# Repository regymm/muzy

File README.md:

# MUZY

AMD/Xilinx ZYNQ 7010/7020 SoC as generic FPGA development board, no DDR -- cheaper than your Artix 7! 

## MUZY-2

[BGA on 2-layers? It's possible and verified!](muzy2.md)

## MUZY-4

[Now on sale!]()

**Hardware**

- Zynq 7020 (xc7z020-clg400-1)

- RP2040-based JTAG blaster, with DirtyJTAG / XVC Pico firmware, working with OpenFPGALoader and Vivado

- Dual SD Card PS + PL

- Dual Video Out HDMI + VGA 

- Dual USB Host

- Dual PMOD

- 2 switches, 2 buttons, 4 LEDs

- 256 Mb (32 MB) SDRAM

Should be perfect for SoC development & work as a handhold FPGA computer! 

Open-source [Zynq](https://github.com/regymm/GenZ)/[FPGA](https://github.com/OpenXC7) toolchains recommended! 

**JTAG**

There're 3 ways to program the FPGA by JTAG: 

1. Use the standard 2x5 pin header with an external Xilinx dongle.
2. Use the on-board pluggable RP2040 module and [the dirtyJtag firwmare](https://github.com/regymm/pico-dirtyJtag), `./pico_fw/dirtyJtag.uf2`. This supports `openFPGALoader -c dirtyJtag bitstream.bit` style direct programming. Simultaneous UART access also available, usually `/dev/ttyACM0`. Vivado access (and thus ILA) not supported by this firmware. 
3. Use the on-board pluggable RP2040 module and [the xvcPico firmware](https://github.com/regymm/xvc-pico), `./pico_fw/xvcPico.uf2`. Then, launch the daemon in xvcPico (`xvcd-pico`) and 127.0.0.1:2542 for XVC access in Vivado. openFPGALoader can still be used with `openFPGALoader -c xvc-client  --ip 127.1 --port 2542 bitstrea.bit`. Simultaneous UART access also available, usually `/dev/ttyACM0`. 

- For RP Pico firmware update, press the BOOT button down while connecting the USB-C cable, a USB-like device will show up on PC for firmware uploading. 

**Software**

Tested: [Zynq PS No-DDR SD Boot](https://github.com/regymm/GenZ/tree/master/examples/6-noddr-sdboot), [RISC-V SoC Linux booting from SD Card](https://github.com/regymm/quasiSoC/tree/master/rtl/hart_transplant/openla500), Dual video output

**Gallery**

Video: [Linux UART with dual graphics test output](https://www.youtube.com/shorts/H9cZ7YbqNOI)

Pictures:

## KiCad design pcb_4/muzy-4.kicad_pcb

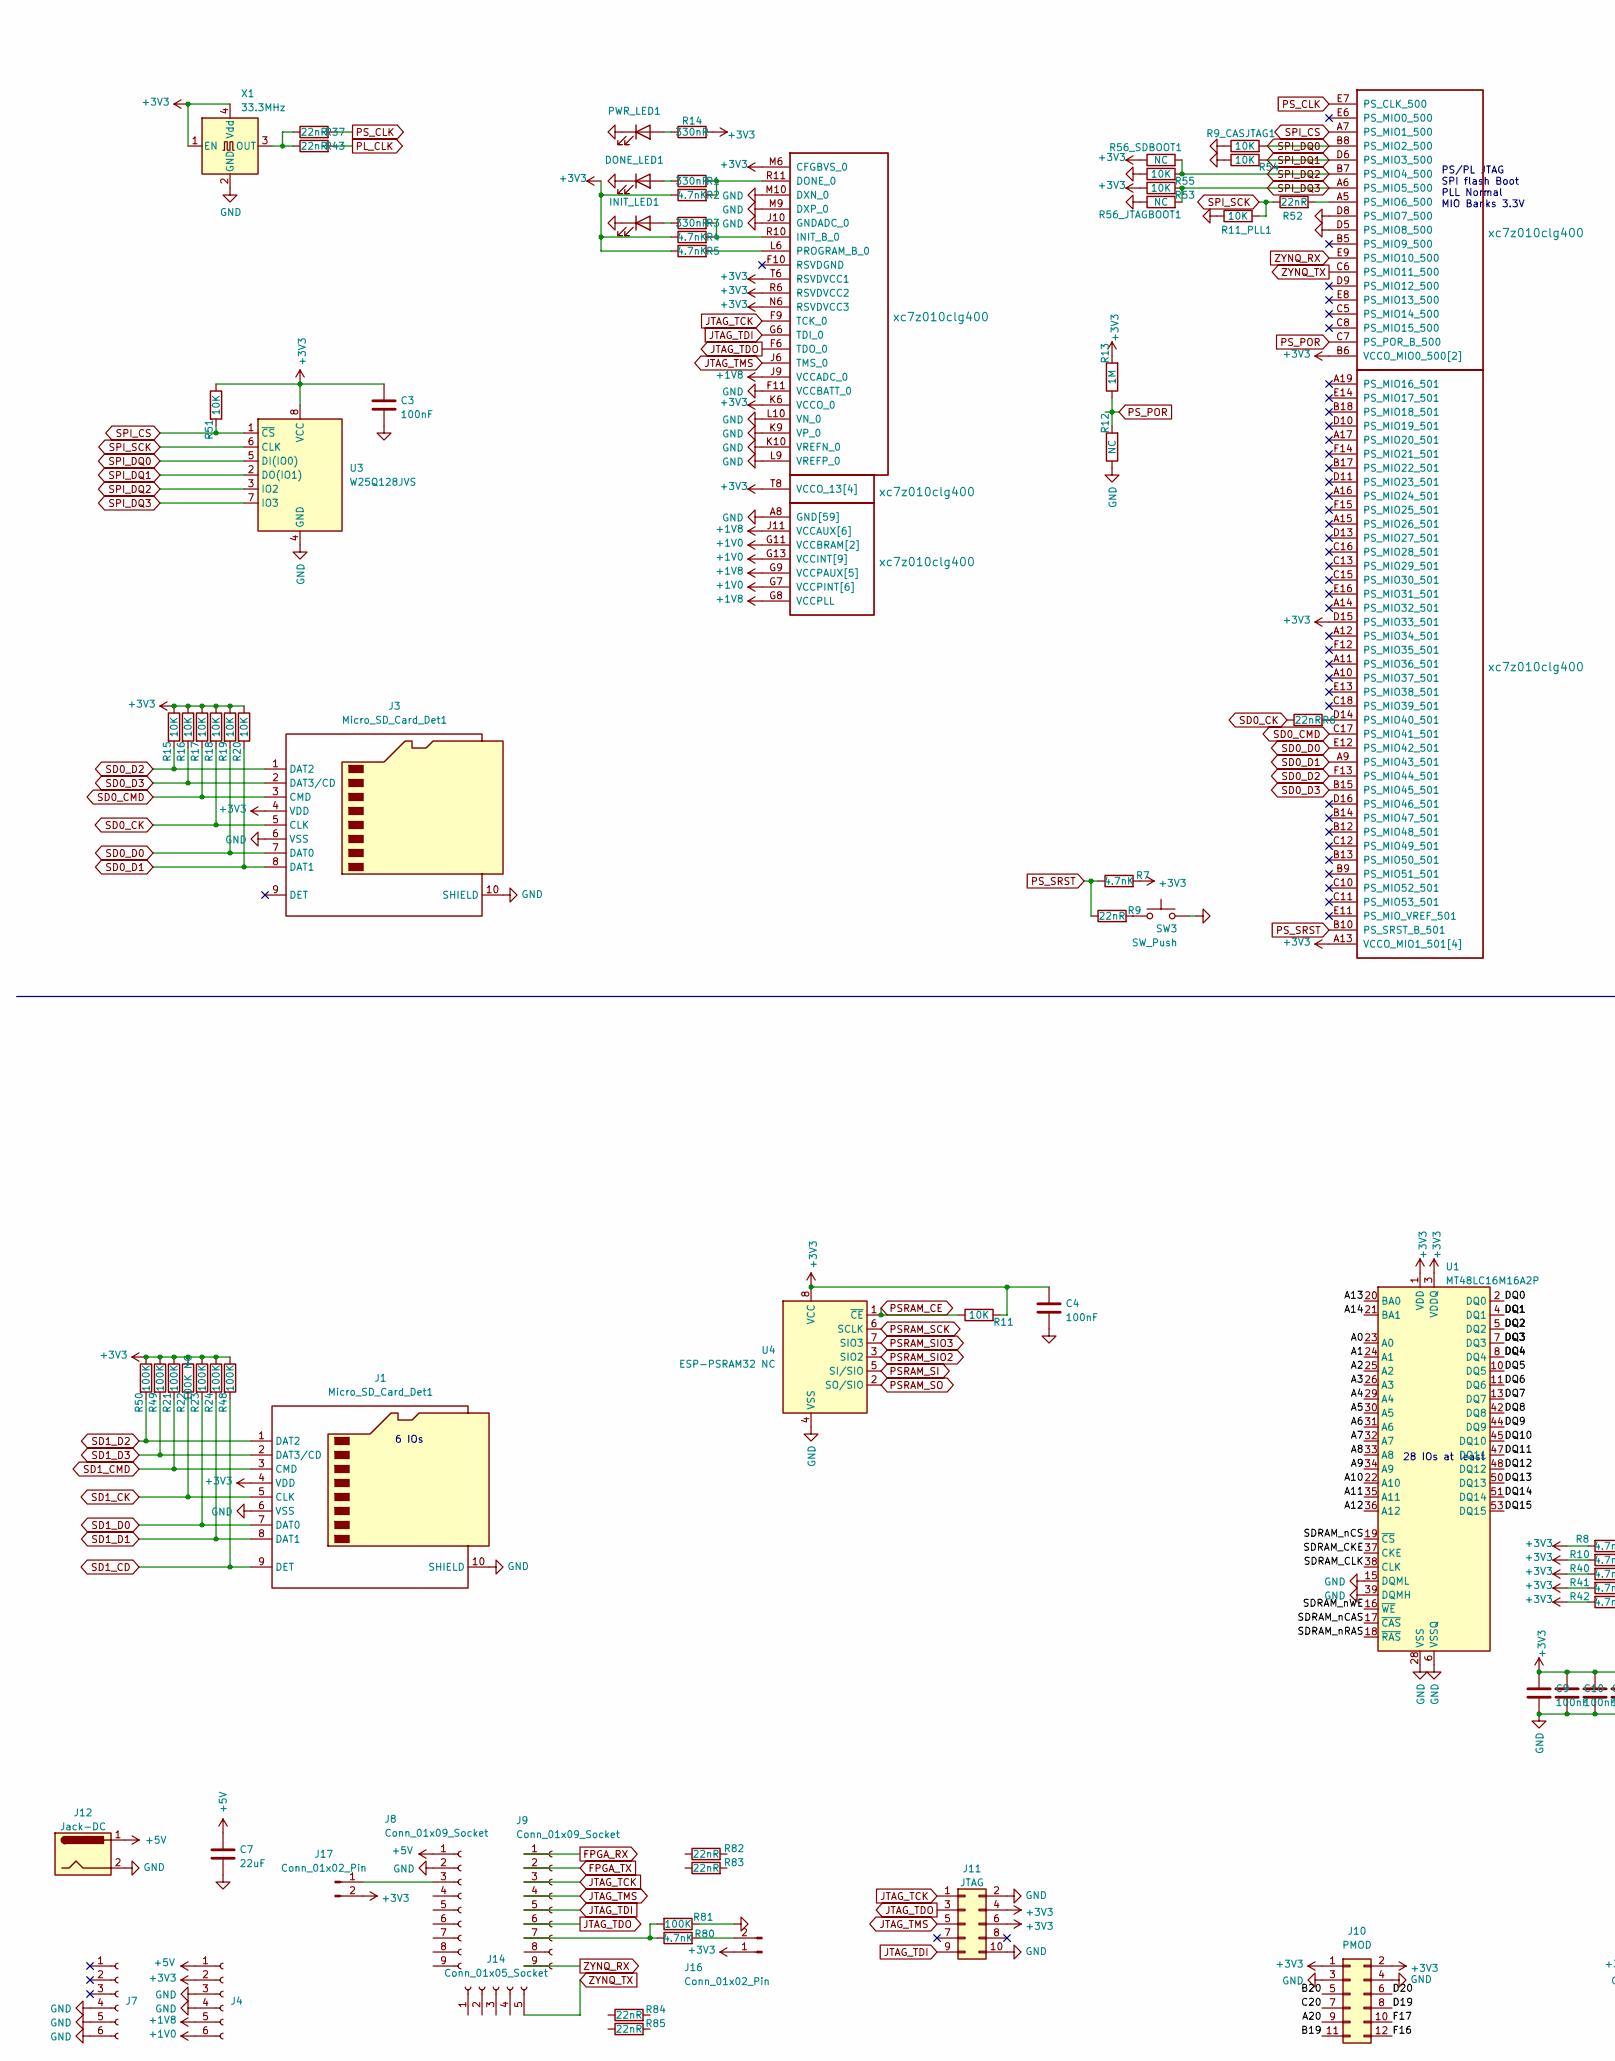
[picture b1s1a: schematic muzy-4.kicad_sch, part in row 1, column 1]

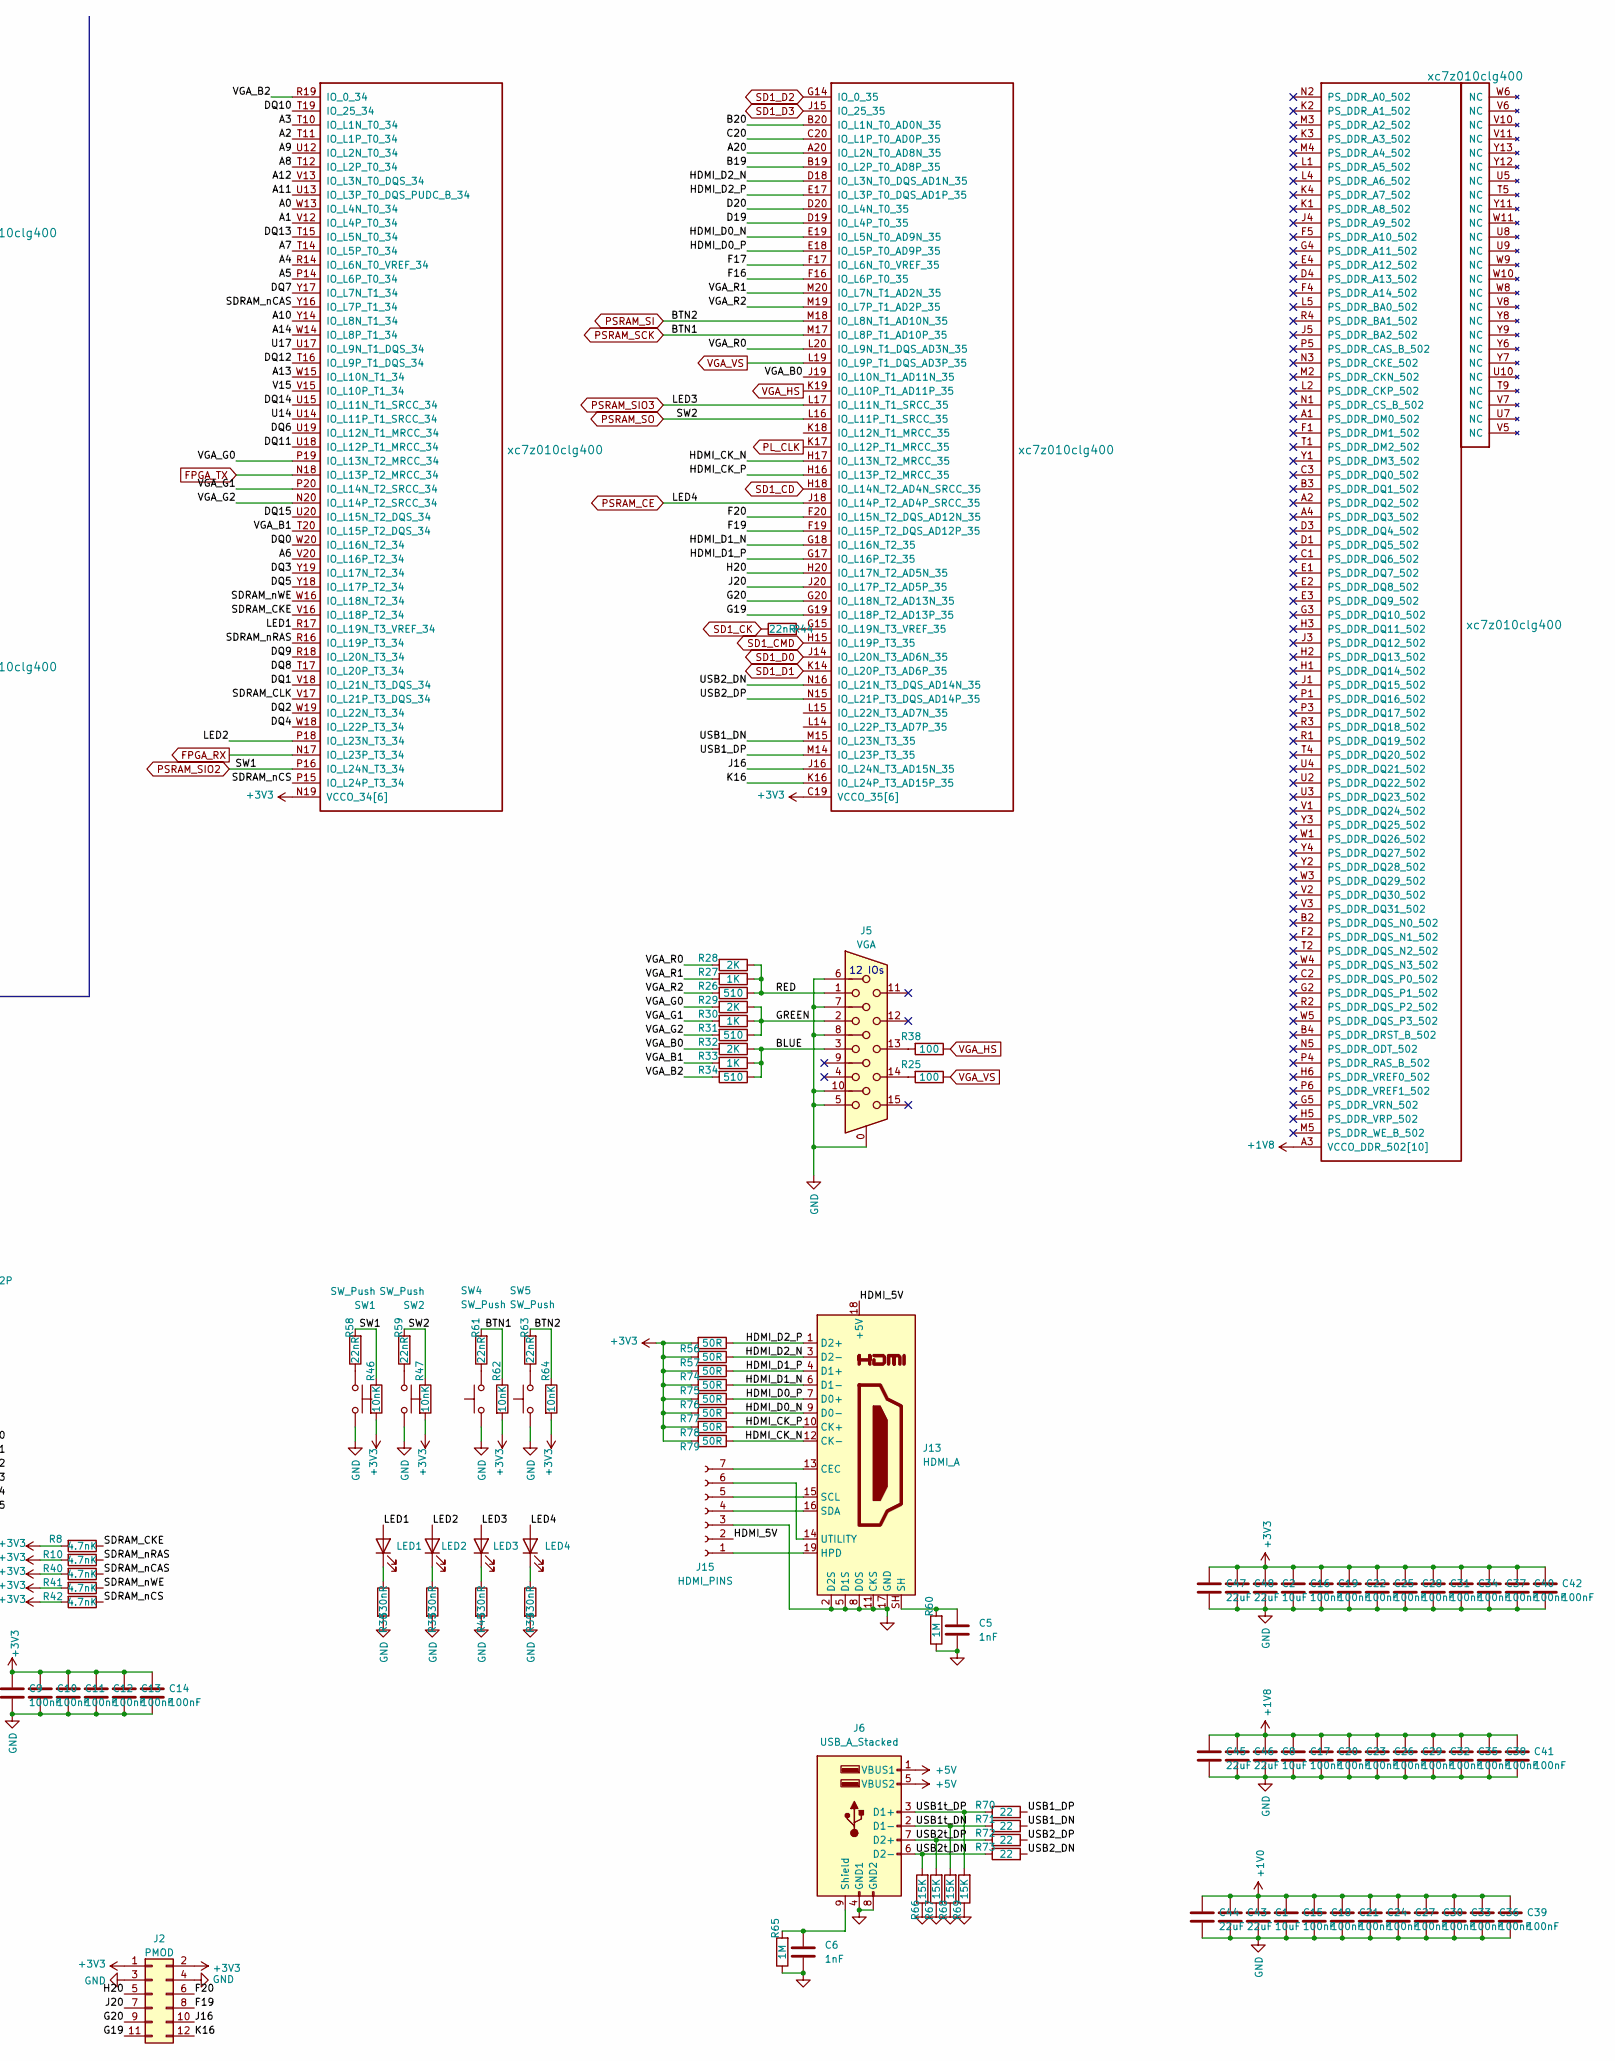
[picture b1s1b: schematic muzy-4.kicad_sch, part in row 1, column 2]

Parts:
C1, C2, C8: 10uF; C_0402_1005Metric
C3, C4, C9, C10, C11, C12, C13, C14, C15, C16, C17, C18, C19, C20, C21, C22, C23, C24, C25, C26, C27, C28, C29, C30, C31, C32, C33, C34, C35, C36, C37, C38, C39, C40, C41, C42: 100nF; C_0402_1005Metric
C5, C6: 1nF; C_0402_1005Metric
C7, C43, C44, C45, C46, C47, C48: 22uF; C_0603_1608Metric
DONE_LED1: LED; LED_0603_1608Metric_Pad1.05x0.95mm_HandSolder
INIT_LED1: LED; LED_0603_1608Metric_Pad1.05x0.95mm_HandSolder
J1, J3: Micro_SD_Card_Det1; SDMICRO_AT
J2, J10: PMOD; PinSocket_2x06_P2.54mm_Horizontal
J4, J7: Conn_01x06_Socket; PinSocket_1x06_P2.54mm_Vertical
J5: VGA; DSUB-15-HD_Female_Horizontal_P2.29x1.98mm_EdgePinOffset3.03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
J6: USB_A_Stacked; USB_A_CUI_UJ2-ADH-TH_Horizontal_Stacked
J8, J9: Conn_01x09_Socket; PinSocket_1x09_P2.54mm_Vertical
J11: JTAG; PinHeader_2x05_P2.54mm_Vertical
J12: Jack-DC; BarrelJack_Wuerth_6941xx301002
J13: HDMI_A; HDMI_A_Molex_208658-1001_Horizontal
J14: Conn_01x05_Socket; PinSocket_1x05_P2.54mm_Vertical
J15: HDMI_PINS; PinSocket_1x07_P1.00mm_Vertical
J16, J17: Conn_01x02_Pin; PinHeader_1x02_P2.54mm_Vertical
LED1, LED2, LED3, LED4: LED; LED_0603_1608Metric_Pad1.05x0.95mm_HandSolder
PWR_LED1: LED; LED_0603_1608Metric_Pad1.05x0.95mm_HandSolder
R1, R3, R14, R35, R36, R39, R45: 330nR; R_0402_1005Metric
R2, R4, R5, R7, R8, R10, R40, R41, R42, R80: 4.7nK; R_0402_1005Metric
R6, R9, R37, R43, R44, R52, R58, R59, R61, R63, R82, R83, R84, R85: 22nR; R_0402_1005Metric
R9_CASJTAG1, R11, R11_PLL1, R15, R16, R17, R18, R19, R20, R51, R53, R54, R55: 10K; R_0402_1005Metric
R12: NC; R_0402_1005Metric_Pad0.72x0.64mm_HandSolder
R13, R65: 1M; R_0402_1005Metric
R21, R23, R24, R48, R49, R50, R81: 100K; R_0402_1005Metric
R22: 100K NC; R_0402_1005Metric
R25, R38: 100; R_0402_1005Metric
R26, R31, R34: 510; R_0402_1005Metric
R27, R30, R33: 1K; R_0402_1005Metric
R28, R29, R32: 2K; R_0402_1005Metric
R46, R47, R62, R64: 10nK; R_0402_1005Metric
R56, R57, R74, R75, R76, R77, R78, R79: 50R; R_0402_1005Metric
R56_JTAGBOOT1, R56_SDBOOT1: NC; R_0402_1005Metric
R60: 1M; R_0402_1005Metric_Pad0.72x0.64mm_HandSolder
R66, R67, R68, R69: 15K; R_0402_1005Metric
R70, R71, R72, R73: 22; R_0402_1005Metric
SW1, SW2: SW_Push; SW_Slide-03_Wuerth-WS-SLTV_10x2.5x6.4_P2.54mm
SW3, SW4, SW5: SW_Push; SW_Push_SPST_NO_Alps_SKRK
U1: MT48LC16M16A2P; TSOP-II-54_22.2x10.16mm_P0.8mm
U2: xc7z010clg400; Xilinx_CLG400_NoPaste_JLC_Package_Delay
U3: W25Q128JVS; SOIC-8_5.23x5.23mm_P1.27mm
U4: ESP-PSRAM32 NC; SOIC-8_3.9x4.9mm_P1.27mm
X1: 33.3MHz; Crystal_SMD_3225-4Pin_3.2x2.5mm

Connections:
+1V0: C1.1, C15.1, C18.1, C21.1, C24.1, C27.1, C30.1, C33.1, C36.1, C39.1, C43.1, C44.1, J4.6, U2.G7 (VCCPINT[6]), U2.G11 (VCCBRAM[2]), U2.G13 (VCCINT[9]), U2.H10 (VCCBRAM[2]), U2.H12 (VCCINT[9]), U2.J7 (VCCPINT[6]), U2.J13 (VCCINT[9]), U2.K12 (VCCINT[9]), U2.L7 (VCCPINT[6]), U2.L13 (VCCINT[9]), U2.M12 (VCCINT[9]), U2.N7 (VCCPINT[6]), U2.N13 (VCCINT[9]), U2.P8 (VCCPINT[6]), U2.P12 (VCCINT[9]), U2.R7 (VCCPINT[6]), U2.R13 (VCCINT[9])
+1V8: C8.1, C17.1, C20.1, C23.1, C26.1, C29.1, C32.1, C35.1, C38.1, C41.1, C45.1, C46.1, J4.5, U2.A3 (VCCO_DDR_502[10]), U2.D2 (VCCO_DDR_502[10]), U2.E5 (VCCO_DDR_502[10]), U2.F8 (VCCPAUX[5]), U2.G1 (VCCO_DDR_502[10]), U2.G8 (VCCPLL), U2.G9 (VCCPAUX[5]), U2.H4 (VCCO_DDR_502[10]), U2.H8 (VCCPAUX[5]), U2.J9 (VCCADC_0), U2.J11 (VCCAUX[6]), U2.K8 (VCCPAUX[5]), U2.L3 (VCCO_DDR_502[10]), U2.L11 (VCCAUX[6]), U2.M8 (VCCPAUX[5]), U2.N9 (VCCAUX[6]), U2.N11 (VCCAUX[6]), U2.P2 (VCCO_DDR_502[10]), U2.P10 (VCCAUX[6]), U2.R5 (VCCO_DDR_502[10]), U2.R9 (VCCAUX[6]), U2.U1 (VCCO_DDR_502[10]), U2.V4 (VCCO_DDR_502[10])
+3V3: C2.1, C3.1, C4.1, C9.1, C10.1, C11.1, C12.1, C13.1, C14.1, C16.1, C19.1, C22.1, C25.1, C28.1, C31.1, C34.1, C37.1, C40.1, C42.1, C47.1, C48.1, J1.4 (VDD), J2.1, J2.2, J3.4 (VDD), J4.2, J10.1, J10.2, J11.4, J11.6, J16.1, J17.2, R2.1, R4.1, R5.1, R7.2, R8.2, R10.2, R11.2, R13.2, R14.2, R15.1, R16.1, R17.1, R18.1, R19.1, R20.1, R21.1, R22.1, R23.1, R24.1, R40.2, R41.2, R42.2, R46.2, R47.2, R48.1, R49.1, R50.1, R51.1, R53.1, R56.2, R56_SDBOOT1.1, R57.2, R62.2, R64.2, R74.2, R75.2, R76.2, R77.2, R78.2, R79.2, U1.1 (VDD), U1.3 (VDDQ), U1.9 (VDDQ), U1.14 (VDD), U1.27 (VDD), U1.43 (VDDQ), U1.49 (VDDQ), U2.A13 (VCCO_MIO1_501[4]), U2.B6 (VCCO_MIO0_500[2]), U2.B16 (VCCO_MIO1_501[4]), U2.C19 (VCCO_35[6]), U2.D7 (VCCO_MIO0_500[2]), U2.D12 (VCCO_MIO1_501[4]), U2.D15 (PS_MIO33_501), U2.E15 (VCCO_MIO1_501[4]), U2.F18 (VCCO_35[6]), U2.H14 (VCCO_35[6]), U2.J17 (VCCO_35[6]), U2.K6 (VCCO_0), U2.K20 (VCCO_35[6]), U2.M6 (CFGBVS_0), U2.M16 (VCCO_35[6]), U2.N6 (RSVDVCC3), U2.N19 (VCCO_34[6]), U2.R6 (RSVDVCC2), U2.R15 (VCCO_34[6]), U2.T6 (RSVDVCC1), U2.T8 (VCCO_13[4]), U2.T18 (VCCO_34[6]), U2.U11 (VCCO_13[4]), U2.V14 (VCCO_34[6]), U2.W7 (VCCO_13[4]), U2.W17 (VCCO_34[6]), U2.Y10 (VCCO_13[4]), U2.Y20 (VCCO_34[6]), U3.8 (VCC), U4.8 (VCC), X1.1 (EN), X1.4 (Vdd)
+5V: C7.1, J4.1, J6.1 (VBUS1), J6.5 (VBUS2), J8.1, J12.1
/A0: U1.23 (A0), U2.W13 (IO_L4N_T0_34)
/A1: U1.24 (A1), U2.V12 (IO_L4P_T0_34)
/A2: U1.25 (A2), U2.T11 (IO_L1P_T0_34)
/A3: U1.26 (A3), U2.T10 (IO_L1N_T0_34)
/A4: U1.29 (A4), U2.R14 (IO_L6N_T0_VREF_34)
/A5: U1.30 (A5), U2.P14 (IO_L6P_T0_34)
/A6: U1.31 (A6), U2.V20 (IO_L16P_T2_34)
/A7: U1.32 (A7), U2.T14 (IO_L5P_T0_34)
/A8: U1.33 (A8), U2.T12 (IO_L2P_T0_34)
/A9: U1.34 (A9), U2.U12 (IO_L2N_T0_34)
/A10: U1.22 (A10), U2.Y14 (IO_L8N_T1_34)
/A11: U1.35 (A11), U2.U13 (IO_L3P_T0_DQS_PUDC_B_34)
/A12: U1.36 (A12), U2.V13 (IO_L3N_T0_DQS_34)
/A13: U1.20 (BA0), U2.W15 (IO_L10N_T1_34)
/A14: U1.21 (BA1), U2.W14 (IO_L8P_T1_34)
/A20: J10.9, U2.A20 (IO_L2N_T0_AD8N_35)
/B19: J10.11, U2.B19 (IO_L2P_T0_AD8P_35)
/B20: J10.5, U2.B20 (IO_L1N_T0_AD0N_35)
/BLUE: J5.3, R32.1, R33.1, R34.1
/C20: J10.7, U2.C20 (IO_L1P_T0_AD0P_35)
/D19: J10.8, U2.D19 (IO_L4P_T0_35)
/D20: J10.6, U2.D20 (IO_L4N_T0_35)
/DQ0: U1.2 (DQ0), U2.W20 (IO_L16N_T2_34)
/DQ1: U1.4 (DQ1), U2.V18 (IO_L21N_T3_DQS_34)
/DQ2: U1.5 (DQ2), U2.W19 (IO_L22N_T3_34)
/DQ3: U1.7 (DQ3), U2.Y19 (IO_L17N_T2_34)
/DQ4: U1.8 (DQ4), U2.W18 (IO_L22P_T3_34)
/DQ5: U1.10 (DQ5), U2.Y18 (IO_L17P_T2_34)
/DQ6: U1.11 (DQ6), U2.U19 (IO_L12N_T1_MRCC_34)
/DQ7: U1.13 (DQ7), U2.Y17 (IO_L7N_T1_34)
/DQ8: U1.42 (DQ8), U2.T17 (IO_L20P_T3_34)
/DQ9: U1.44 (DQ9), U2.R18 (IO_L20N_T3_34)
/DQ10: U1.45 (DQ10), U2.T19 (IO_25_34)
/DQ11: U1.47 (DQ11), U2.U18 (IO_L12P_T1_MRCC_34)
/DQ12: U1.48 (DQ12), U2.T16 (IO_L9P_T1_DQS_34)
/DQ13: U1.50 (DQ13), U2.T15 (IO_L5N_T0_34)
/DQ14: U1.51 (DQ14), U2.U15 (IO_L11N_T1_SRCC_34)
/DQ15: U1.53 (DQ15), U2.U20 (IO_L15N_T2_DQS_34)
/F16: J10.12, U2.F16 (IO_L6P_T0_35)
/F17: J10.10, U2.F17 (IO_L6N_T0_VREF_35)
/F19: J2.8, U2.F19 (IO_L15P_T2_DQS_AD12P_35)
/F20: J2.6, U2.F20 (IO_L15N_T2_DQS_AD12N_35)
/G19: J2.11, U2.G19 (IO_L18P_T2_AD13P_35)
/G20: J2.9, U2.G20 (IO_L18N_T2_AD13N_35)
/GREEN: J5.2, R29.1, R30.1, R31.1
/H20: J2.5, U2.H20 (IO_L17N_T2_AD5N_35)
/HDMI_5V: J13.18 (+5V), J15.2
/HDMI_CK_N: J13.12 (CK-), R79.1, U2.H17 (IO_L13N_T2_MRCC_35)
/HDMI_CK_P: J13.10 (CK+), R78.1, U2.H16 (IO_L13P_T2_MRCC_35)
/HDMI_D0_N: J13.9 (D0-), R77.1, U2.E19 (IO_L5N_T0_AD9N_35)
/HDMI_D0_P: J13.7 (D0+), R76.1, U2.E18 (IO_L5P_T0_AD9P_35)
/HDMI_D1_N: J13.6 (D1-), R75.1, U2.G18 (IO_L16N_T2_35)
/HDMI_D1_P: J13.4 (D1+), R74.1, U2.G17 (IO_L16P_T2_35)
/HDMI_D2_N: J13.3 (D2-), R57.1, U2.D18 (IO_L3N_T0_DQS_AD1N_35)
/HDMI_D2_P: J13.1 (D2+), R56.1, U2.E17 (IO_L3P_T0_DQS_AD1P_35)
/J16: J2.10, U2.J16 (IO_L24N_T3_AD15N_35)
/J20: J2.7, U2.J20 (IO_L17P_T2_AD5P_35)
/K16: J2.12, U2.K16 (IO_L24P_T3_AD15P_35)
/LED1: LED1.2 (A), U2.R17 (IO_L19N_T3_VREF_34)
/LED2: LED2.2 (A), U2.P18 (IO_L23N_T3_34)
/RED: J5.1, R26.1, R27.1, R28.1
/SDRAM_CKE: R8.1, U1.37 (CKE), U2.V16 (IO_L18P_T2_34)
/SDRAM_CLK: U1.38 (CLK), U2.V17 (IO_L21P_T3_DQS_34)
/SDRAM_nCAS: R40.1, U1.17 (~CAS), U2.Y16 (IO_L7P_T1_34)
/SDRAM_nCS: R42.1, U1.19 (~CS), U2.P15 (IO_L24P_T3_34)
/SDRAM_nRAS: R10.1, U1.18 (~RAS), U2.R16 (IO_L19P_T3_34)
/SDRAM_nWE: R41.1, U1.16 (~WE), U2.W16 (IO_L18N_T2_34)
/U14: U2.U14 (IO_L11P_T1_SRCC_34)
/U17: U2.U17 (IO_L9N_T1_DQS_34)
/USB1_DN: R71.2, U2.M15 (IO_L23N_T3_35)
/USB1_DP: R70.2, U2.M14 (IO_L23P_T3_35)
/USB1t_DN: J6.2 (D1-), R68.2, R71.1
/USB1t_DP: J6.3 (D1+), R69.2, R70.1
/USB2_DN: R73.2, U2.N16 (IO_L21N_T3_DQS_AD14N_35)
/USB2_DP: R72.2, U2.N15 (IO_L21P_T3_DQS_AD14P_35)
/USB2t_DN: J6.6 (D2-), R66.2, R73.1
/USB2t_DP: J6.7 (D2+), R67.2, R72.1
/V15: U2.V15 (IO_L10P_T1_34)
/VGA_B0: R32.2, U2.J19 (IO_L10N_T1_AD11N_35)
/VGA_B1: R33.2, U2.T20 (IO_L15P_T2_DQS_34)
/VGA_B2: R34.2, U2.R19 (IO_0_34)
/VGA_G0: R29.2, U2.P19 (IO_L13N_T2_MRCC_34)
/VGA_G1: R30.2, U2.P20 (IO_L14N_T2_SRCC_34)
/VGA_G2: R31.2, U2.N20 (IO_L14P_T2_SRCC_34)
/VGA_R0: R28.2, U2.L20 (IO_L9N_T1_DQS_AD3N_35)
/VGA_R1: R27.2, U2.M20 (IO_L7N_T1_AD2N_35)
/VGA_R2: R26.2, U2.M19 (IO_L7P_T1_AD2P_35)
FPGA_RX: J9.1, U2.N17 (IO_L23P_T3_34)
FPGA_TX: J9.2, U2.N18 (IO_L13P_T2_MRCC_34)
GND: C1.2, C2.2, C3.2, C4.2, C5.2, C6.2, C7.2, C8.2, C9.2, C10.2, C11.2, C12.2, C13.2, C14.2, C15.2, C16.2, C17.2, C18.2, C19.2, C20.2, C21.2, C22.2, C23.2, C24.2, C25.2, C26.2, C27.2, C28.2, C29.2, C30.2, C31.2, C32.2, C33.2, C34.2, C35.2, C36.2, C37.2, C38.2, C39.2, C40.2, C41.2, C42.2, C43.2, C44.2, C45.2, C46.2, C47.2, C48.2, DONE_LED1.1 (K), INIT_LED1.1 (K), J1.6 (VSS), J1.10 (SHIELD), J2.3, J2.4, J3.6 (VSS), J3.10 (SHIELD), J4.3, J4.4, J5.0, J5.5, J5.6, J5.7, J5.8, J5.10, J6.4 (GND1), J6.8 (GND2), J7.4, J7.5, J7.6, J8.2, J10.3, J10.4, J11.2, J11.10, J12.2, J13.2 (D2S), J13.5 (D1S), J13.8 (D0S), J13.11 (CKS), J13.17 (GND), J15.3, PWR_LED1.1 (K), R9_CASJTAG1.1, R11_PLL1.1, R12.1, R35.2, R36.2, R39.2, R45.2, R54.1, R55.1, R56_JTAGBOOT1.1, R60.1, R65.1, R66.1, R67.1, R68.1, R69.1, R81.1, SW1.2, SW2.2, SW3.2, SW4.1, SW5.1, U1.6 (VSSQ), U1.12 (VSSQ), U1.15 (DQML), U1.28 (VSS), U1.39 (DQMH), U1.41 (VSS), U1.46 (VSSQ), U1.52 (VSSQ), U1.54 (VSS), U2.A8 (GND[59]), U2.A18 (GND[59]), U2.B1 (GND[59]), U2.B11 (GND[59]), U2.C4 (GND[59]), U2.C9 (GND[59]), U2.C14 (GND[59]), U2.D5 (PS_MIO8_500), U2.D8 (PS_MIO7_500), U2.D17 (GND[59]), U2.E10 (GND[59]), U2.E20 (GND[59]), U2.F3 (GND[59]), U2.F7 (GND[59]), U2.F11 (VCCBATT_0), U2.G10 (GND[59]), U2.G12 (GND[59]), U2.G16 (GND[59]), U2.H7 (GND[59]), U2.H9 (GND[59]), U2.H11 (GND[59]), U2.H13 (GND[59]), U2.H19 (GND[59]), U2.J2 (GND[59]), U2.J8 (GND[59]), U2.J10 (GNDADC_0), U2.J12 (GND[59]), U2.K5 (GND[59]), U2.K7 (GND[59]), U2.K9 (VP_0), U2.K10 (VREFN_0), U2.K11 (GND[59]), U2.K13 (GND[59]), U2.K15 (GND[59]), U2.L8 (GND[59]), U2.L9 (VREFP_0), U2.L10 (VN_0), U2.L12 (GND[59]), U2.L18 (GND[59]), U2.M1 (GND[59]), U2.M7 (GND[59]), U2.M9 (DXP_0), U2.M10 (DXN_0), U2.M11 (GND[59]), U2.M13 (GND[59]), U2.N4 (GND[59]), U2.N8 (GND[59]), U2.N10 (GND[59]), U2.N12 (GND[59]), U2.N14 (GND[59]), U2.P7 (GND[59]), U2.P9 (GND[59]), U2.P11 (GND[59]), U2.P13 (GND[59]), U2.P17 (GND[59]), U2.R8 (GND[59]), U2.R12 (GND[59]), U2.R20 (GND[59]), U2.T3 (GND[59]), U2.T7 (GND[59]), U2.T13 (GND[59]), U2.U6 (GND[59]), U2.U16 (GND[59]), U2.V9 (GND[59]), U2.V19 (GND[59]), U2.W2 (GND[59]), U2.W12 (GND[59]), U2.Y5 (GND[59]), U2.Y15 (GND[59]), U3.4 (GND), U4.4 (VSS), X1.2 (GND)
JTAG_TCK: J9.3, J11.1, U2.F9 (TCK_0)
JTAG_TDI: J9.5, J11.9, U2.G6 (TDI_0)
JTAG_TDO: J9.6, J11.3, U2.F6 (TDO_0)
JTAG_TMS: J9.4, J11.5, U2.J6 (TMS_0)
unnamed: C5.1, J13.SH, R60.2
unnamed: DONE_LED1.2 (A), R1.1
unnamed: INIT_LED1.2 (A), R3.1
unnamed: J5.13, R38.2
unnamed: J5.14, R25.2
unnamed: C6.1, J6.9 (Shield), R65.2
unnamed: J9.7, R80.1, R81.2
unnamed: J13.13 (CEC), J15.7
unnamed: J13.19 (HPD), J15.1
unnamed: J13.15 (SCL), J15.5
unnamed: J13.16 (SDA), J15.4
unnamed: J13.14 (UTILITY), J15.6
unnamed: J16.2, R80.2
unnamed: J8.3, J17.1
unnamed: LED1.1 (K), R36.1
unnamed: LED2.1 (K), R35.1
unnamed: LED3.1 (K), R45.1
unnamed: LED4.1 (K), R39.1
unnamed: PWR_LED1.2 (A), R14.1
unnamed: R9.2, SW3.1
unnamed: R58.1, SW1.1
unnamed: R59.1, SW2.1
unnamed: R61.1, SW4.2
unnamed: R63.1, SW5.2
unnamed: R1.2, R2.2, U2.R11 (DONE_0)
unnamed: R3.2, R4.2, U2.R10 (INIT_B_0)
unnamed: R5.2, U2.L6 (PROGRAM_B_0)
unnamed: R44.2, U2.G15 (IO_L19N_T3_VREF_35)
unnamed: R52.2, U2.A5 (PS_MIO6_500)
unnamed: R6.2, U2.D14 (PS_MIO40_501)
unnamed: R37.1, R43.1, X1.3 (OUT)
PL_CLK: R43.2, U2.K17 (IO_L12P_T1_MRCC_35)
PSRAM_CE: LED4.2 (A), R11.1, U2.J18 (IO_L14P_T2_AD4P_SRCC_35), U4.1 (~CE)
PSRAM_SCK: R61.2, R62.1, U2.M17 (IO_L8P_T1_AD10P_35), U4.6 (SCLK)
PSRAM_SI: R63.2, R64.1, U2.M18 (IO_L8N_T1_AD10N_35), U4.5 (SI/SIO)
PSRAM_SIO2: R46.1, R58.2, U2.P16 (IO_L24N_T3_34), U4.3 (SIO2)
PSRAM_SIO3: LED3.2 (A), U2.L17 (IO_L11N_T1_SRCC_35), U4.7 (SIO3)
PSRAM_SO: R47.1, R59.2, U2.L16 (IO_L11P_T1_SRCC_35), U4.2 (SO/SIO)
PS_CLK: R37.2, U2.E7 (PS_CLK_500)
PS_POR: R12.2, R13.1, U2.C7 (PS_POR_B_500)
PS_SRST: R7.1, R9.1, U2.B10 (PS_SRST_B_501)
SD0_CK: J3.5 (CLK), R6.1, R18.2
SD0_CMD: J3.3 (CMD), R17.2, U2.C17 (PS_MIO41_501)
SD0_D0: J3.7 (DAT0), R19.2, U2.E12 (PS_MIO42_501)
SD0_D1: J3.8 (DAT1), R20.2, U2.A9 (PS_MIO43_501)
SD0_D2: J3.1 (DAT2), R15.2, U2.F13 (PS_MIO44_501)
SD0_D3: J3.2 (DAT3/CD), R16.2, U2.B15 (PS_MIO45_501)
SD1_CD: J1.9 (DET), R48.2, U2.H18 (IO_L14N_T2_AD4N_SRCC_35)
SD1_CK: J1.5 (CLK), R22.2, R44.1
SD1_CMD: J1.3 (CMD), R21.2, U2.H15 (IO_L19P_T3_35)
SD1_D0: J1.7 (DAT0), R23.2, U2.J14 (IO_L20N_T3_AD6N_35)
SD1_D1: J1.8 (DAT1), R24.2, U2.K14 (IO_L20P_T3_AD6P_35)
SD1_D2: J1.1 (DAT2), R50.2, U2.G14 (IO_0_35)
SD1_D3: J1.2 (DAT3/CD), R49.2, U2.J15 (IO_25_35)
SPI_CS: R51.2, U2.A7 (PS_MIO1_500), U3.1 (~CS)
SPI_DQ0: R9_CASJTAG1.2, U2.B8 (PS_MIO2_500), U3.5 (DI(IO0))
SPI_DQ1: R54.2, U2.D6 (PS_MIO3_500), U3.2 (DO(IO1))
SPI_DQ2: R55.2, R56_SDBOOT1.2, U2.B7 (PS_MIO4_500), U3.3 (IO2)
SPI_DQ3: R53.2, R56_JTAGBOOT1.2, U2.A6 (PS_MIO5_500), U3.7 (IO3)
SPI_SCK: R11_PLL1.2, R52.1, U3.6 (CLK)
VGA_HS: R38.1, U2.K19 (IO_L10P_T1_AD11P_35)
VGA_VS: R25.1, U2.L19 (IO_L9P_T1_DQS_AD3P_35)
ZYNQ_RX: J9.9, U2.E9 (PS_MIO10_500)
ZYNQ_TX: J14.5, U2.C6 (PS_MIO11_500)

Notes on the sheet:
6 IOs
28 IOs at least
PS/PL JTAG SPI flash Boot PLL Normal MIO Banks 3.3V
12 IOs

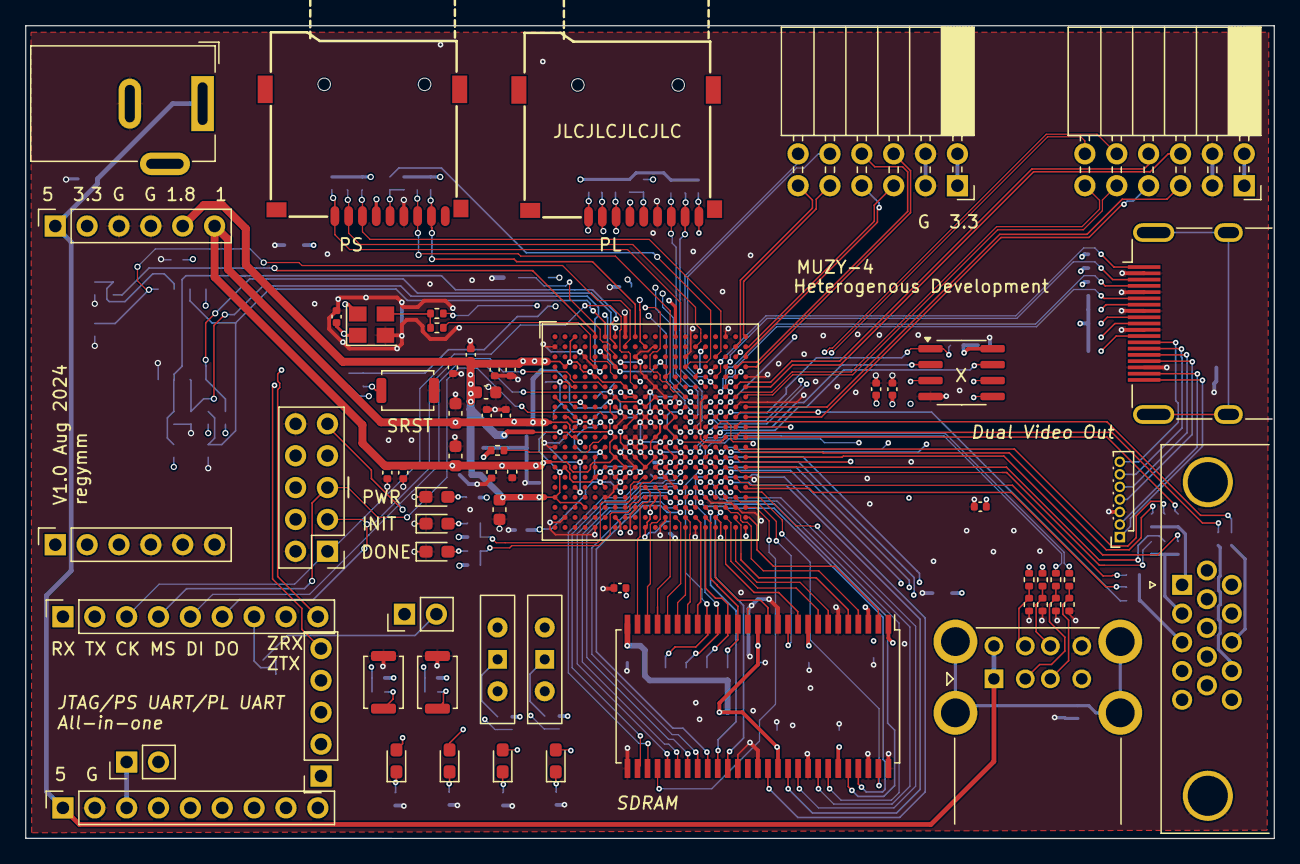
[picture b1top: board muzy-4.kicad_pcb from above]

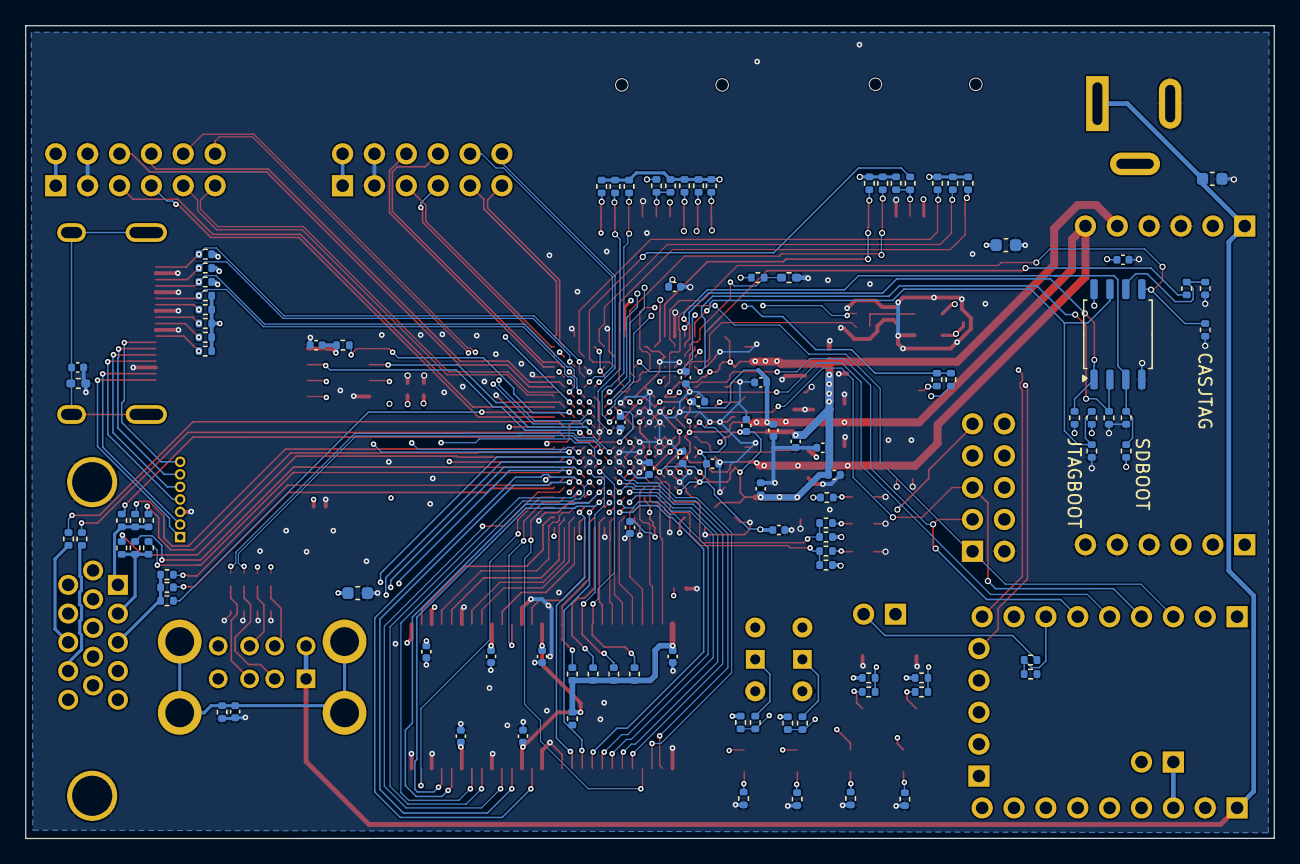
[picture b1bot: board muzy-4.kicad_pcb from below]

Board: 4 copper layers, 99.5 x 64.8 mm, 167 parts (104 on the bottom side), 159 nets.
